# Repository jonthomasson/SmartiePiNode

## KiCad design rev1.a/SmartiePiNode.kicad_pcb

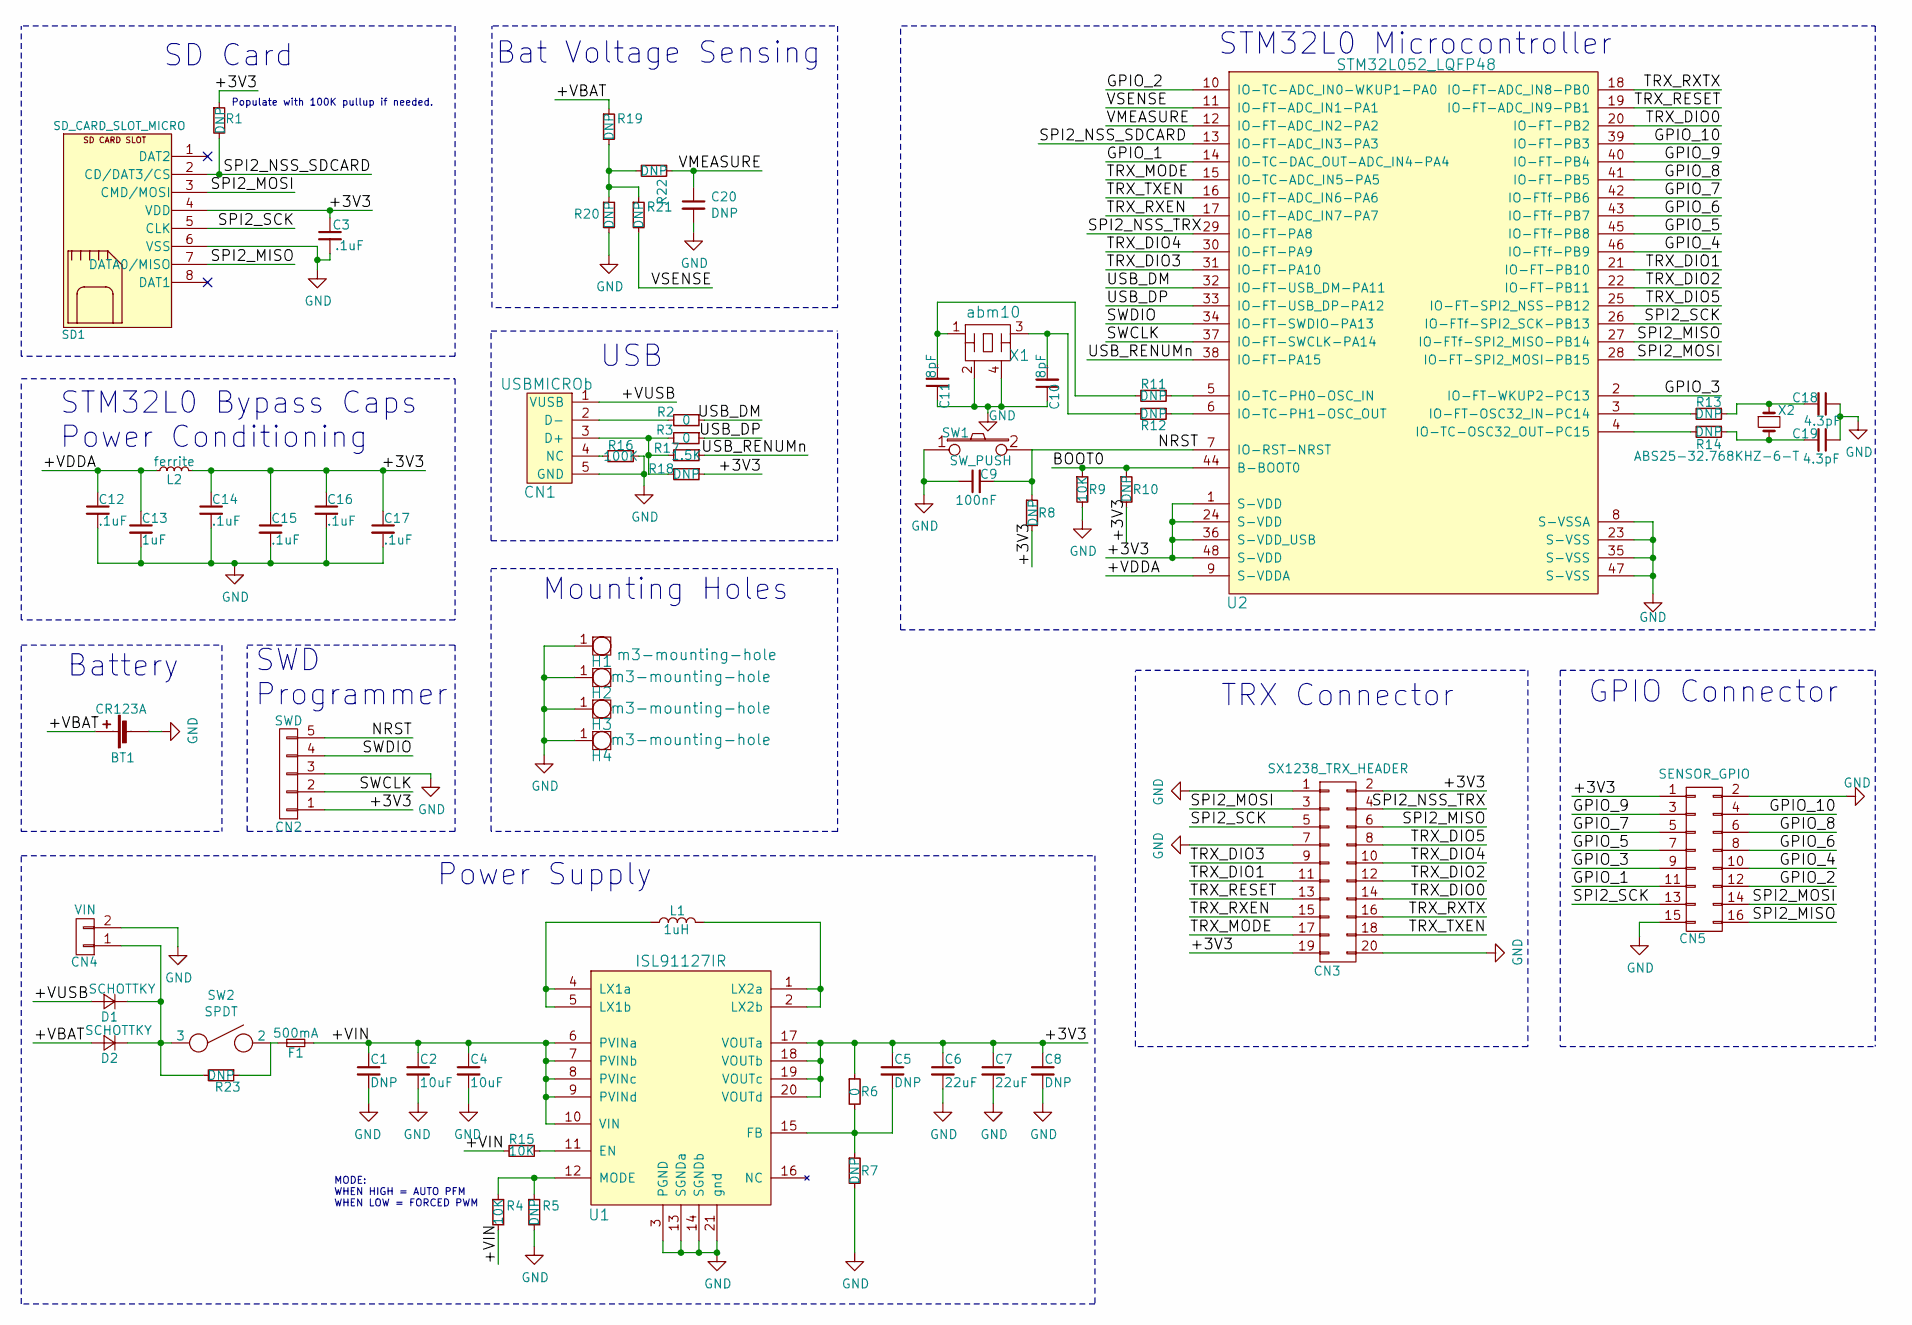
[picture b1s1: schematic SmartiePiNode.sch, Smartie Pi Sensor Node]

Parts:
BT1: CR123A; mpd-BH123A
C1: DNP; C_0805
C2, C4: 10uF; C_0603
C3, C12, C14, C15, C16, C17: .1uF; C_0603
C5, C8, C20: DNP; C_0603
C6, C7: 22uF; C_0603
C9: 100nF; C_0603
C10, C11: 8pF; C_0603
C13: 1uF; C_0603
C18, C19: 4.3pF; C_0603
CN1: USBMICROb; amphenol-microusb-10118194
CN2: SWD; Pin_Header_Straight_1x05
CN3: SX1238_TRX_HEADER; sx1238_trx
CN4: VIN; Pin_Header_Straight_1x02
CN5: SENSOR_GPIO; Pin_Header_Straight_2x08
D1, D2: SCHOTTKY; onsemi-NRVB120VLSFT1G
F1: 500mA; belfuse-c2q
H1, H2, H3, H4: m3-mounting-hole
L1: 1uH; murata-1277AS-H-1R0M
L2: ferrite; MH1608-601Y
R1, R5, R7, R8, R10, R11, R12, R13, R14, R18, R19, R20, R21, R22, R23: DNP; R_0603
R2, R3, R6: 0; R_0603
R4, R9, R15: 10K; R_0603
R16: 100K; R_0603
R17: 1.5K; R_0603
SD1: SD_CARD_SLOT_MICRO; amphenol-microsd-1140084168
SW1: SW_PUSH; SWITCH_1825966_1
SW2: SPDT; copal-cl-sb-12a
U1: ISL91127IR; intersil-isl91127ir
U2: STM32L052_LQFP48; STM32L052C8T6
X1: abm10; abracon-abm10
X2: ABS25-32.768KHZ-6-T; abracon-abs07

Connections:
/+3V3: C3.1, C5.1, C6.1, C7.1, C8.1, C14.1, C15.1, C16.1, C17.1, CN2.1, CN3.2, CN3.19, CN5.1, L2.2, R1.1, R6.1, R8.2, R10.2, R18.1, SD1.4 (VDD), U1.17 (VOUTa), U1.18 (VOUTb), U1.19 (VOUTc), U1.20 (VOUTd), U2.1 (S-VDD), U2.24 (S-VDD), U2.36 (S-VDD_USB), U2.48 (S-VDD)
/+VBAT: BT1.1 (+), D2.2 (A), R19.1
/+VDDA: C12.1, C13.1, L2.1, U2.9 (S-VDDA)
/+VIN: C1.1, C2.1, C4.1, F1.2, R4.2, R15.2, U1.6 (PVINa), U1.7 (PVINb), U1.8 (PVINc), U1.9 (PVINd), U1.10 (VIN)
/+VUSB: CN1.1 (VUSB), D1.2 (A)
/BOOT0: R9.1, R10.1, U2.44 (B-BOOT0)
/GPIO_1: CN5.11, U2.14 (IO-TC-DAC_OUT-ADC_IN4-PA4)
/GPIO_2: CN5.12, U2.10 (IO-TC-ADC_IN0-WKUP1-PA0)
/GPIO_3: CN5.9, U2.2 (IO-FT-WKUP2-PC13)
/GPIO_4: CN5.10, U2.46 (IO-FTf-PB9)
/GPIO_5: CN5.7, U2.45 (IO-FTf-PB8)
/GPIO_6: CN5.8, U2.43 (IO-FTf-PB7)
/GPIO_7: CN5.5, U2.42 (IO-FTf-PB6)
/GPIO_8: CN5.6, U2.41 (IO-FT-PB5)
/GPIO_9: CN5.3, U2.40 (IO-FT-PB4)
/GPIO_10: CN5.4, U2.39 (IO-FT-PB3)
/NRST: C9.2, CN2.5, R8.1, SW1.2, U2.7 (IO-RST-NRST)
/SPI2_MISO: CN3.6, CN5.16, SD1.7 (DATA0/MISO), U2.27 (IO-FTf-SPI2_MISO-PB14)
/SPI2_MOSI: CN3.3, CN5.14, SD1.3 (CMD/MOSI), U2.28 (IO-FT-SPI2_MOSI-PB15)
/SPI2_NSS_SDCARD: R1.2, SD1.2 (CD/DAT3/CS), U2.13 (IO-FT-ADC_IN3-PA3)
/SPI2_NSS_TRX: CN3.4, U2.29 (IO-FT-PA8)
/SPI2_SCK: CN3.5, CN5.13, SD1.5 (CLK), U2.26 (IO-FTf-SPI2_SCK-PB13)
/SWCLK: CN2.2, U2.37 (IO-FT-SWCLK-PA14)
/SWDIO: CN2.4, U2.34 (IO-FT-SWDIO-PA13)
/TRX_DIO0: CN3.14, U2.20 (IO-FT-PB2)
/TRX_DIO1: CN3.11, U2.21 (IO-FT-PB10)
/TRX_DIO2: CN3.12, U2.22 (IO-FT-PB11)
/TRX_DIO3: CN3.9, U2.31 (IO-FT-PA10)
/TRX_DIO4: CN3.10, U2.30 (IO-FT-PA9)
/TRX_DIO5: CN3.8, U2.25 (IO-FT-SPI2_NSS-PB12)
/TRX_MODE: CN3.17, U2.15 (IO-TC-ADC_IN5-PA5)
/TRX_RESET: CN3.13, U2.19 (IO-FT-ADC_IN9-PB1)
/TRX_RXEN: CN3.15, U2.17 (IO-FT-ADC_IN7-PA7)
/TRX_RXTX: CN3.16, U2.18 (IO-FT-ADC_IN8-PB0)
/TRX_TXEN: CN3.18, U2.16 (IO-FT-ADC_IN6-PA6)
/USB_DM: R2.1, U2.32 (IO-FT-USB_DM-PA11)
/USB_DP: R3.1, U2.33 (IO-FT-USB_DP-PA12)
/USB_RENUMn: R17.1, U2.38 (IO-FT-PA15)
/VMEASURE: C20.1, R22.1, U2.12 (IO-FT-ADC_IN2-PA2)
/VSENSE: R21.2, U2.11 (IO-FT-ADC_IN1-PA1)
GND: BT1.2 (-), C1.2, C2.2, C3.2, C4.2, C6.2, C7.2, C8.2, C9.1, C10.1, C11.1, C12.2, C13.2, C14.2, C15.2, C16.2, C17.2, C18.1, C19.1, C20.2, CN1.5 (GND), CN2.3, CN3.1, CN3.7, CN3.20, CN4.2, CN5.2, CN5.15, H1.1, H2.1, H3.1, H4.1, R5.2, R7.2, R9.2, R16.1, R20.2, SD1.6 (VSS), SW1.1, U1.3 (PGND), U1.13 (SGNDa), U1.14 (SGNDb), U1.21 (gnd), U2.8 (S-VSSA), U2.23 (S-VSS), U2.35 (S-VSS), U2.47 (S-VSS), X1.2, X1.4
unnamed: C5.2, R6.2, R7.1, U1.15 (FB)
unnamed: C10.2, R12.2, X1.3
unnamed: C11.2, R11.2, X1.1
unnamed: C18.2, R13.1, X2.2
unnamed: C19.2, R14.1, X2.1
unnamed: CN1.2 (D-), R2.2
unnamed: CN1.3 (D+), R3.2, R17.2, R18.2
unnamed: CN1.4 (NC), R16.2
unnamed: CN4.1, D1.1 (K), D2.1 (K), R23.2, SW2.3
unnamed: F1.1, R23.1, SW2.2
unnamed: L1.1, U1.4 (LX1a), U1.5 (LX1b)
unnamed: L1.2, U1.1 (LX2a), U1.2 (LX2b)
unnamed: R4.1, R5.1, U1.12 (MODE)
unnamed: R11.1, U2.5 (IO-TC-PH0-OSC_IN)
unnamed: R12.1, U2.6 (IO-TC-PH1-OSC_OUT)
unnamed: R13.2, U2.3 (IO-FT-OSC32_IN-PC14)
unnamed: R14.2, U2.4 (IO-TC-OSC32_OUT-PC15)
unnamed: R15.1, U1.11 (EN)
unnamed: R19.2, R20.1, R21.1, R22.2

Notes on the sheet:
Populate with 100K pullup if needed.
Bat Voltage Sensing
MODE: WHEN HIGH = AUTO PFM WHEN LOW = FORCED PWM
SD Card
Battery
SWD Programmer
USB
STM32L0 Bypass Caps Power Conditioning
Power Supply
STM32L0 Microcontroller
Mounting Holes
TRX Connector
GPIO Connector

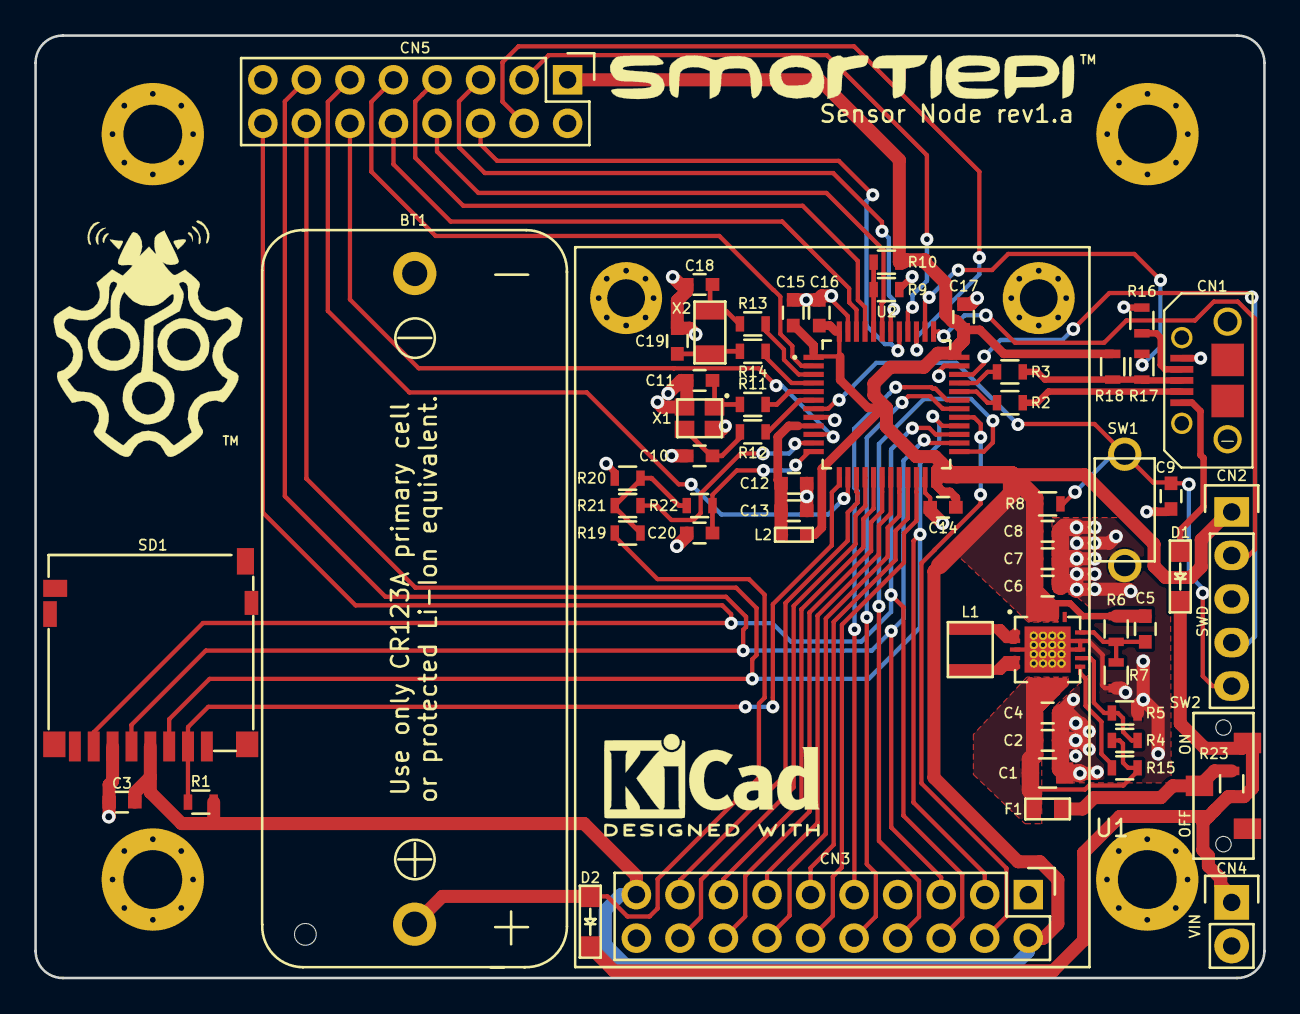
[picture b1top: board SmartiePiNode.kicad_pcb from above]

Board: 2 copper layers, 71.7 x 55.0 mm, 65 parts (0 on the bottom side), 60 nets.

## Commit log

2018-05-22 :octocat: Added .gitattributes & .gitignore files
2018-05-22 Initial checkin. Added SMPS circuit.
2018-05-22 more work on the SMPS.
2018-05-24 more schematic work. Starting on stm32l052_lqfp48 symbol.
2018-05-24 more schematic work. Finished stm32.
2018-05-25 more schematic changes. USB and reset.
2018-05-26 stm32 oscillators and programming interface.
2018-05-26 stm32 spi2
2018-05-27 sd card schematic interface
2018-05-27 finished trx header, battery, power broker circuit, sd card.
2018-05-27 added ST-Link programming interface connector.
2018-05-28 bypass caps for stm32
2018-05-28 added a protection fuse
2018-05-29 started footprint generation
2018-05-31 footprints
2018-06-01 finished battery footprint (BH123A) and 3d model.
2018-06-01 more battery holder modeling and footprint
2018-06-02 hse selection and footprint
2018-06-03 L1 part selection, footprint and 3d model creation.
2018-06-03 sw1 selection footprint and 3d model
2018-06-05 x1 and x2 footprint and 3d models added to cvpcb
2018-06-05 fuse f1 footprint and 3d model added
2018-06-06 stm32l052 footprint and 3d model added
2018-06-06 stm32l052 cvpcb
2018-06-06 l2 ferrite bead footprint and 3d model
2018-06-06 intersil isl91127ir footprint and 3d model
2018-06-07 d1 and d2 schotky diode footprint and 3d models
2018-06-07 double check and fix footprints
2018-06-08 new abm10 schematic symbol and circuitry
2018-06-10 starting pcb layout/design
2018-06-10 finished board outline with mounting holes
2018-06-11 footprint for sx1238 trx module
2018-06-12 starting pcb components placement
2018-06-13 more pcb layout/parts placement.
2018-06-13 more placement and layout.
2018-06-14 more layout
2018-06-15 tweaking final layout a bit more.
2018-06-15 more schematic/usb verification.
2018-06-16 footprint placement and tweaking continued...
2018-06-18 usb and schematic changes/tweaks.
2018-06-18 added battery sensing circuit and a bit more work on usb.
2018-06-19 battery sense circuit and new footprint for voltage reg.
2018-06-19 more pcb layout
2018-06-19 finalizing layout
2018-06-21 optimizing nets
2018-06-22 starting psu/vcc and ground traces.
2018-06-23 figuring out traces for trx and power lines.
2018-06-23 finished routing trx
2018-06-25 finished ground and initial net traces
2018-06-26 more routing of trx and sd card
2018-06-29 everything routed except sensor io header
2018-06-30 created net for sensor gpio header
2018-07-03 finished routing of rev1.a
2018-07-10 added optional power switch
2018-07-10 a few more silk screen and power trace tweaks
2018-07-13 working on smartie pi logo iterations
2018-07-13 first pass with logo and text on silk screen
2018-07-14 more logo tweaks
2018-07-14 more power supply and track optimizing
2018-07-14 finished a few 3d renderings of the board
2018-07-16 cleaning up schematic and pcb a bit.
2018-07-16 added list of supported enclosures to pcb.
2018-07-18 added more schematic capture images
2018-07-27 added tm for logo
2018-07-27 adding gerbers
2018-07-28 added gerbers
2018-07-28 added bom
2018-11-23 added new logo with FREEDOM font.
2019-11-09 upgraded project to kicad 5. Fixing some board outline issues
2020-05-02 updated 3d shapes to kicad 5 naming

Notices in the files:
rev1.a/SmartiePiNode.kicad_pcb:
© Jon Thomasson 2018
